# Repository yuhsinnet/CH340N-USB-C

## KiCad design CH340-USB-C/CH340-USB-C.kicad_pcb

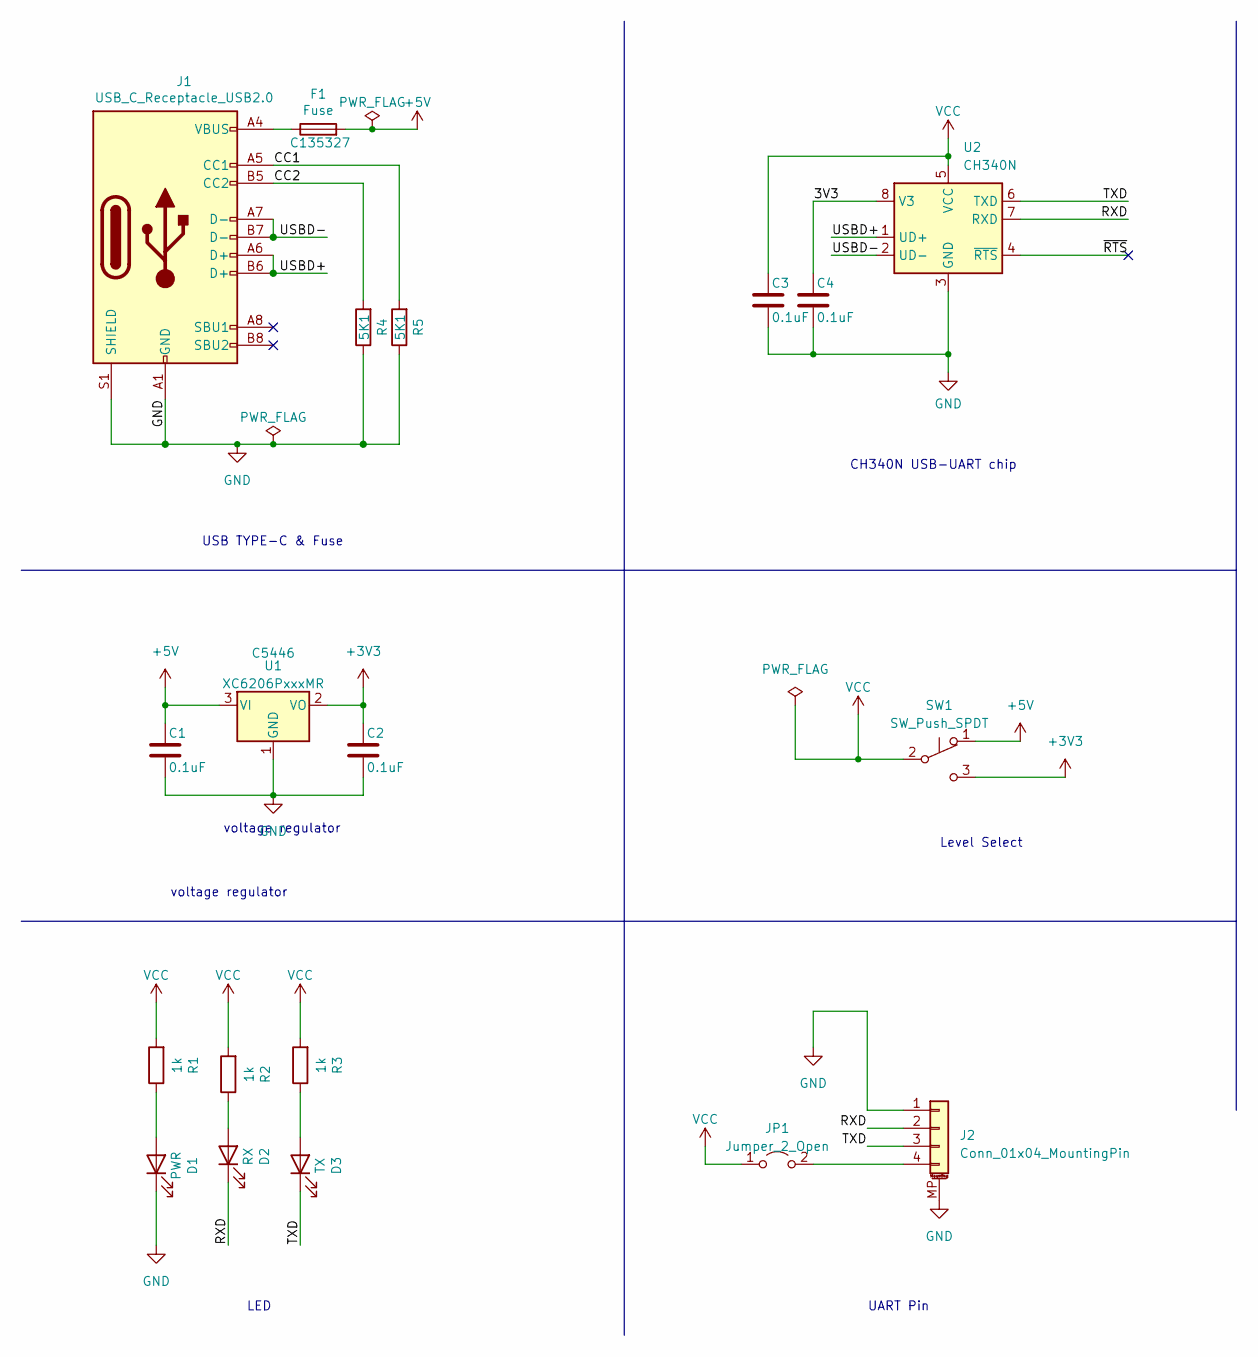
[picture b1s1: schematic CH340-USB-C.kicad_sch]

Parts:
C1, C2: 0.1uF; C_0805_2012Metric; LCSC C49678
C3, C4: 0.1uF; C_0805_2012Metric
D1: PWR; LED_0805_2012Metric; LCSC C84256
D2: RX; LED_0805_2012Metric; LCSC C84256
D3: TX; LED_0805_2012Metric; LCSC C84256
F1: Fuse; Fuse_0805_2012Metric; LCSC C135327
J1: USB_C_Receptacle_USB2.0; USB_C_Receptacle_HRO_TYPE-C-31-M-12
J2: Conn_01x04_MountingPin; JST_PH_S4B-XH-SM4-TB_1x04-1MP_P2.50mm_Horizontal
JP1: Jumper_2_Open; SolderJumper-2_P1.3mm_Open_RoundedPad1.0x1.5mm
R1, R2, R3: 1k; R_0805_2012Metric; LCSC C17513
R4, R5: 5K1; R_0805_2012Metric; LCSC C27834
SW1: SW_Push_SPDT; SolderJumper-3_P1.3mm_Bridged12_Pad1.0x1.5mm
U1: XC6206PxxxMR; SOT-23-3; LCSC C5446
U2: CH340N; SOIC-8_3.9x4.9mm_P1.27mm; LCSC C2977777

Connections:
+3V3: C2.1, SW1.3 (C), U1.2 (VO)
+5V: C1.1, F1.2, SW1.1 (A), U1.3 (VI)
/3V3: C4.1, U2.8 (V3)
/CC1: J1.A5 (CC1), R5.2
/CC2: J1.B5 (CC2), R4.2
/RXD: D2.1 (K), J2.2, U2.7 (RXD)
/TXD: D3.1 (K), J2.3, U2.6 (TXD)
/USBD+: J1.A6 (D+), J1.B6 (D+), U2.1 (UD+)
/USBD-: J1.A7 (D-), J1.B7 (D-), U2.2 (UD-)
/~RTS: U2.4 (~RTS)
GND: C1.2, C2.2, C3.2, C4.2, D1.1 (K), J1.A1 (GND), J1.A12 (GND), J1.B1 (GND), J1.B12 (GND), J1.S1 (SHIELD), J2.1, J2.MP (MountPin), R4.1, R5.1, U1.1 (GND), U2.3 (GND)
unnamed: D1.2 (A), R1.1
unnamed: D2.2 (A), R2.1
unnamed: D3.2 (A), R3.1
unnamed: F1.1, J1.A4 (VBUS), J1.A9 (VBUS), J1.B4 (VBUS), J1.B9 (VBUS)
unnamed: J2.4, JP1.2 (B)
VCC: C3.1, JP1.1 (A), R1.2, R2.2, R3.2, SW1.2 (B), U2.5 (VCC)

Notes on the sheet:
LED
USB TYPE-C & Fuse
UART Pin
voltage regulator
Level Select
CH340N USB-UART chip

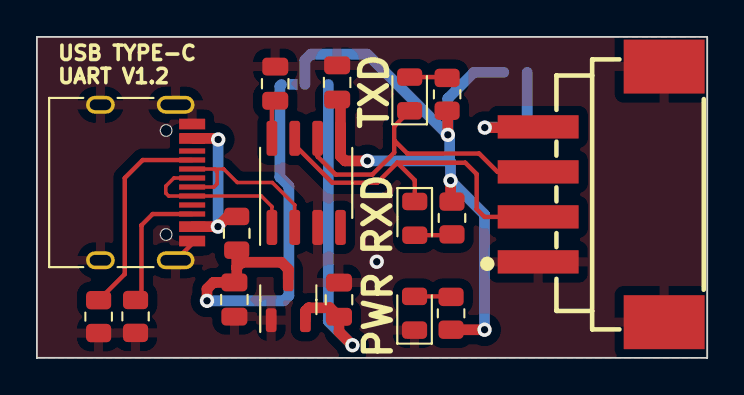
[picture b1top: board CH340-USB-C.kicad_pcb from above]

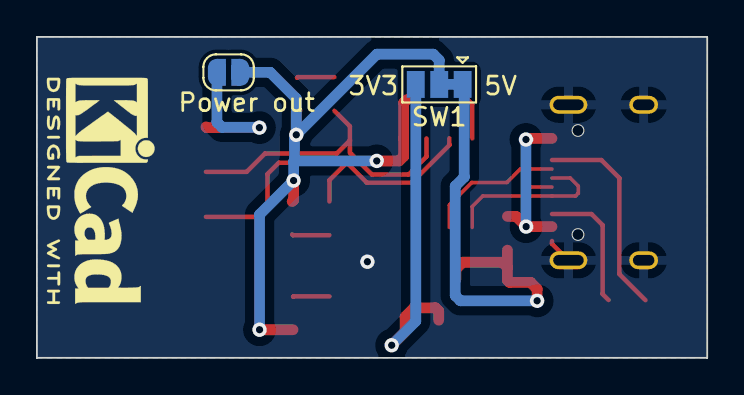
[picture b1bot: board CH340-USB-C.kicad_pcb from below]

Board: 2 copper layers, 37.2 x 17.8 mm, 19 parts (2 on the bottom side), 16 nets.

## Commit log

2022-03-26 創建專案、原理圖
2022-03-27 add LDO
    Linear Voltage Regulators XC6206
2022-03-27 add Device
    add 3v3 Led & SPDT Switch Voltage
2022-03-27 remove Pwr LED
2022-03-27 調整
    調整版面
    新增保險絲LCSC 編號
2022-03-27 Update CH340-USB-C.kicad_sch
    增加編號
2022-03-27 update 原理圖
2022-03-27 初步排好電路板
2022-03-27 放置零件及佈線
2022-03-28 調整布局
2022-03-28 重新鋪銅
2022-03-28 fix 電路板零件屬性及用料
2022-03-28 Generate JLCPCB file
2022-03-29 新佈局&USB 信號
2022-03-29 更新佈局
2022-03-29 鋪銅絲印
2022-03-29 JLCPCB
2022-03-29 up jlcpcb
2022-03-29 將排真座排除BOM
2022-03-29 update JLCPCB
2022-03-30 add text
2022-03-31 update pcb layout
2023-04-30 新增功能
    1.可以對外輸出電源
    2.可以切換電壓准位
2023-04-30 Update CH340-USB-C.kicad_pcb
    移除電容器編號絲印
2023-04-30 新增
    1.可以選擇是否輸出電源(預設"不輸出")
2023-04-30 Update CH340-USB-C.kicad_pcb
    將電源輸出選擇改到底層
2023-05-05 Update CH340-USB-C.kicad_pcb
    移除SW1 字樣
2023-05-05 增加絲印
    增加公司名稱及腳位名稱
